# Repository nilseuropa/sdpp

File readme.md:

# SD Card to Parallel Port Adapter(s) and MS-DOS Driver

"A long forgotten solution that gets updated every decade or so. [ 1994 - 2014 - **2024** ]"
*It's either the update rate is doubling - and the next update will come in 2029 - or it is coming in every year that ends with a four...* Anyway, I wanted to have a single repository to contain all information to keep this neat solution afloat. This is it.

## Parallel port power
Current version of the MS-DOS driver supports [powering the SD card](https://www.transkommunikation.ch/dateien/schaltungen/diverse_schaltungen/computer_circuits/Get%20Power%20From%20Pc%20Parallel%20Port.pdf) via the parallel port. A modern micro SD card [takes around 25mA](
https://goughlui.com/2021/02/27/experiment-microsd-card-power-consumption-spi-performance/) of current on 3.3V in average. There are five data channels that are utilized as power outputs:

| Adapter | DB-25 Pin | Parallel Port |
| -------- | ------- | ------- |
| VCC | 5 | Data 3 |
| VCC | 6 | Data 4 |
| VCC | 7 | Data 5 |
| VCC | 8 | Data 6 |
| VCC | 9 | Data 7 |

*IEEE 1284 Level II interface drivers must be able to source 14 mA current (at least +2.4V
voltage) and also sink 14 mA current (output voltage lower than 0.4V). The output impedance
in normal operation range is defined to be 50+/-5 ohms.*

|Port type|Normal|UM82C11-C|IEEE 1284|
| -------- | -------- | ------- | ------- |
Data output (>2.4V)| 2.6 mA| 2 mA| 14 mA|
Data line sink (<0.4V)| 24 mA| 24 mA| 14 mA|
Control output (>2.4 V)| 0.5 mA| 1.5 mA| ?|
Signal lines (short circuit)| 1 mA| ?| ?|
Control line sink (<0.4V)| 7 mA| 7 mA| 14 mA|

:warning: **WARNING, using this feature can potentially harm your port driver if it is not IEEE1284 compliant!**

As this standard came alive in 1994, rule of thumb is that most computers built after it are probably compliant, and everything before that is a mystery that you have to solve for the sake of your machine.
The power feature is totally optional, and potentially dangerous if your machine doesn't support it.

# Hardware options

1. Hook up an SD breakout board to a DB25 and be done with it *( see Wiring )*
2. Etch my simple adapter board design for the breakout module
3. Build my SD Drive design *( contributions are welcome )*

## SD Breakout board
In principle any SD card connector breakout board can be used that has 3.3/5V level shifters and a voltage regulator - like this one:

:warning: **Do not use breakout boards without level shifters! You will most likely damage your card.**

### Wiring
| SD Adapter | Hint | DB-25 Pin | Parallel Port |
| -------- | ------- | ------- | ------- |
| CS |Chip select| 4 | Data 2 |
| SCK |Clock| 3 | Data 1 |
| MOSI |Card serial in| 2 | Data 0 |
| MISO |Card serial out| 13 | Select |
| VCC |**+5V DC**|   |  |
| GND |Ground| 25 | Ground |
| **Optional** |  | |
| CD |Card detect| 11 | BUSY|

## Breakout Adapter

### Schematic diagram
Disregard the barrier diodes in case you want to build a fool-proof circuit.

### Etch it yourself at home board
This is an easy to fabricate adapter board for the micro SD card connector breakout module depicted above. It is available through at least 5 vendors. *( The one I have came from Reichelt. )*

**Double check that your port is IEEE1284 compliant.**
The circuit also provides an auxiliary power input through barrel jack connector. In case you are unsure or your port is unable to handle the load **DO NOT POPULATE** the barrier diodes!

## SD Drive *( the fancy )*
Or a more integrated version, designed to power the SD card through an IEEE1284 compliant port.

### Schematic diagram

Each channel is fed through a super low forward drop *(0.31V)* barrier diode to protect the port in case the push-pull outputs are operated by another software than the MS-DOS driver in this repository. The sum of the channels is buffered by a 100uF capacitor, and the supply voltage for the SD card is provided by a linear regulator. With the correct port type, this provides around 100mA on the 3.3V rail that can handle the microsecond long spikes that occur during flash write cycles.

### Board layout

**Double check that your port is IEEE1284 compliant.**
The circuit also provides an auxiliary power input through a USB-C connector. In case you are unsure or your port is unable to handle the load **DO NOT POPULATE** the barrier diodes!

#### Bill of materials
```
Part     Value          Package             Type

C1       1.0uF          0603-CAP
C2       1.0uF          0603-CAP
C3       0.1uF          0603-CAP
C4       0.1uF          0603-CAP
C5       100uF          PANASONIC_C
D1       CGRM4001-G     SOD-123_MINI-SMA   RB521ASA
D2       CGRM4001-G     SOD-123_MINI-SMA   RB521ASA
D3       CGRM4001-G     SOD-123_MINI-SMA   RB521ASA
D4       CGRM4001-G     SOD-123_MINI-SMA   RB521ASA
D5       CGRM4001-G     SOD-123_MINI-SMARB521ASA
J1       1-2295018-2    TE_1-2295018-2     USB-C
JP2      USD_CONNECTOR  MICRO-SD-SOCKET-PP 4UCON-15882
R1       100k           0603-RES
R2       100k           0603-RES
R3       100k           0603-RES
R4       100k           0603-RES
U1       IC1            SO14               TXB0104PWRSOIC14
U2       3.3V           SOT23-5            V_REG_AP2112K-3.3V
X1       SUB-D DB25     F25D
```

:exclamation: This printed circuit board is yet to be tested. If you have built one, please let me know.

****

# MS-DOS Device Driver
Original device driver is written in 1994 by **Dan Marks** and it is based on TU58 by **Robert Armstrong**. Foolproof MMCv3/SDv1/SDv2 control module from Chan Fat FS has been added by [profdc9](https://forum.vcfed.org/index.php?threads/ms-dos-driver-for-an-sd-card-connected-via-a-parallel-port.41516/) and posted on Vintage Computer Federation forum in 2014.

The driver is made available under the GNU General Public License version 2 and incorporates modified code from ELM Chan Fat FS: http://elm-chan.org/fsw/ff/00index_e.html.

#### Compilation
If you would like to compile the driver from source you'll need **Borland C++ 3.1** with the included **Turbo Assembler 3.1** installed on your DOS machine.

### Binaries

:floppy_disk: [Download](driver/SD.SYS) the latest pre-compiled version of `SD.SYS`

:floppy_disk: [Download](driver/NILQUAD.SYS) a modified version compiled for Nilquader's NC100 SD adapter `NILQUAD.SYS` *(MISO on BUSY)*

****

## How to use it

* Create <=32MB partition(s) on a uSD card
* Format to FAT16 for best results
* Find out the port base of your parallel port
* Make sure that you are powering the adapter correctly
* Install the [driver](driver/SD.SYS) :arrow_up: on DOS and enjoy. *(see configuration below)*

#### Prepare the card on Linux
1. Open a terminal
2. Find your block device with `lsblk`
3. `sudo umount /dev/<device_partition>` -- unmount if mounted
4. Partition with `sudo fdisk /dev/<dev_name>` -- or use *gparted*
  * `p` lists, `d` deletes, `n` for new partition
  * new partition --> `p` for primary
  * enter last sector `+32M`
  * `t` to change partition type to FAT16 (`L` to list avaiable formats )
  * `w` to write changes to partition table
5. Format `sudo mkdosfs -F 16 /dev/<dev_name>`

#### Prepare the card on Windows

1. Open a command line and start `diskpart`
2. `list disk` -- find the disk number of your card
3. `select disk #` -- select your sd card
4. `list part` -- look for existing partitions
5. `select part #` -- select the partition to work with
6. `delete part #` -- to get rid of anything that is not FAT16
7. `create part primary size=32` -- create a 32MB partition
8. `exit` -- leave diskpart
9. `format X: /FS:FAT /Q` -- format partition to FAT16 (replace X)

[Source](https://aesmit.org/2020/05/24/format-sd-card-fat16-on-windows-10/)

#### Prepare the card on Mac
1. Open Terminal (Applications > Utilities)
2. `hdiutil create -size 32m -fs "MS-DOS FAT16" -volname "MSDOS32MB" mydisk.dmg` -- create a blank 32MB FAT16 disk image
3. `hdiutil attach mydisk.dmg` -- mount image
4. Copy your files
5. `hdiutil detach /Volumes/MSDOS32MB` -- unmout image
6. `hdiutil convert mydisk.dmg -format UDTO -o mydisk.iso` -- convert to raw format (mydisk.iso.cdr)
7. Use `diskutil list` to find your physical media
8. Unmount it if mounted `diskutil unmountDisk /dev/disk#`
9. `sudo dd if=mydisk.iso.cdr of=/dev/rdisk2 bs=1m` -- write your image to the partition
10. `diskutil eject /dev/disk#` -- eject card

### DOS
Put the following line in your `config.sys` file in order to install and load the driver:

`DEVICE=SD.SYS /p=<partition #> /b=<port base index>`

```
/d = debugging mode (displays copious debugging messsages)
/k = use card detect signal to inform DOS that card is attached
/p = partition number (1-4) to partition in MBR to use.  Default: first available.
/b = port base index of parallel port, one of
     1=0x3BC, 2=0x378, 3=0x278, 4=0x3E8, 5=0x2E8
     Default: 0x378
```
#### Notes
You can have multiple copies of the driver loaded if there are multiple partitions on your SD card you want to use simultaneously.

****

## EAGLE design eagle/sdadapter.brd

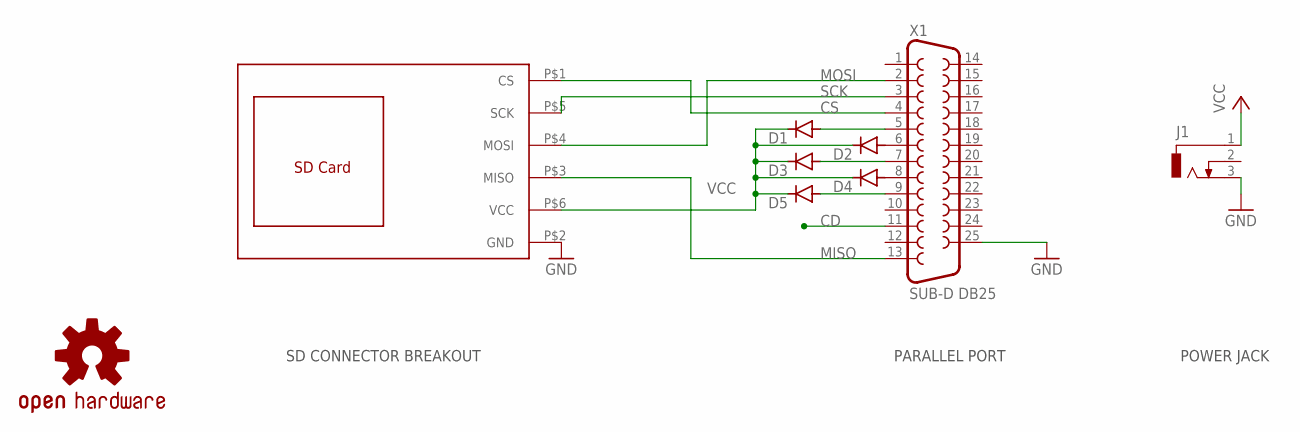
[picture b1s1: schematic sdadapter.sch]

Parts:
D1, D2, D3, D4, D5: CGRM4001-G; SOD-123_MINI-SMA
J1: DCJ0303
LOGO2: OSHW-LOGOS; OSHW-LOGO-S
U$1: SD_ADAPTER; DEBO_MICRO_SD
X1: SUB-D DB25; F25D

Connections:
CD: X1.11
CS: U$1.P$1 (CS), X1.4
GND: J1.3, U$1.P$2 (GND), X1.25
MISO: U$1.P$3 (MISO), X1.13
MOSI: U$1.P$4 (MOSI), X1.2
unnamed: D1.A, X1.5
unnamed: D2.A, X1.6
unnamed: D3.A, X1.7
unnamed: D4.A, X1.8
unnamed: D5.A, X1.9
SCK: U$1.P$5 (SCK), X1.3
VCC: D1.C, D2.C, D3.C, D4.C, D5.C, J1.1, U$1.P$6 (VCC)

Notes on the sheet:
PARALLEL PORT
SD CONNECTOR BREAKOUT
POWER JACK

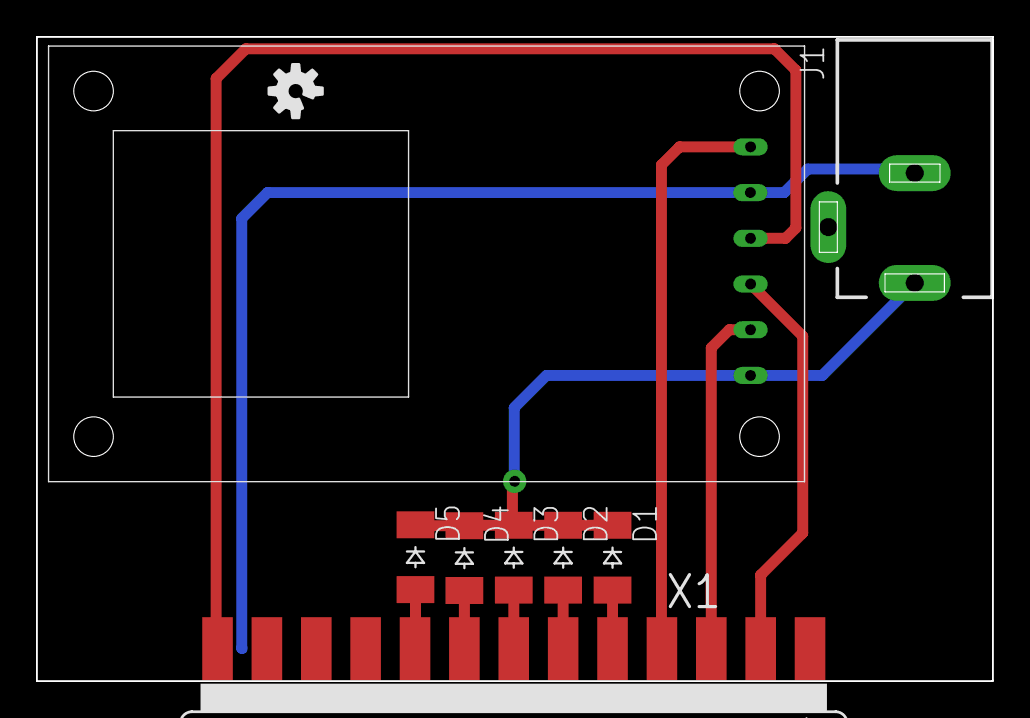
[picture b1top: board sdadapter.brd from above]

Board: 2 copper layers, 53.1 x 35.8 mm, 9 parts (0 on the bottom side), 11 nets.

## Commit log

2024-03-01 Cirtcuit and Driver source files added
2024-03-02 how to section
2024-03-03 module adapter board

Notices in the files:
parts and their libraries:
SparkFun-Aesthetics: Licensing: Creative Commons ShareAlike 4.0 International - https://creativecommons.org/licenses/by-sa/4.0
